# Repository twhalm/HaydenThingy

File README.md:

# Readme
- I am not a pro so I am sure things are a bit messy
- This uses KiCad 8.x
- The initial production and assembly quote was through JLCPCB
## Overview
If you want to get started and just view things in KiCad:
- Clone the repo
- Download KiCad
- Open the haydenThingy project

There will be a lot of stuff in the folder but there are really only two things to look at: the HaydenThingy schematic and pcb.  You can view those by opening the Schematic editor and the PCB editor.

## Initial version of the board
The first version of the board just combines the connections of the original three boards onto one PCB.  The ESP-32 and the LTE board attach via headers and the RS-485 breakout board was just incorporated into the PCB.

The larger board is a pretty simple board, all of the components are one once side, it is a large rectangle, and there are M3 holes for mounting on each corner.

## Next Steps
- Probably the first thing to do with this board is to order a low-volume run as a prototype to ensure everything fits/works as intended.

### Easy improvements to make
These are obvious and easy things that could be changed.
- The positioning of all of the components can be changed to make things slightly more compact or better
- You can make it more compact by mouting components on both sides (you can probably mount the LTE and ESP-32 boards on the front and back)
- Mounting holes can be changed and more can be added.

### Medium improvements to make?
- Put the battery connector on the PCB if it makes things easier
- Get rid of the screw terminal and put downstream components on the board directly (jst connectors for sensors, etc)

### Hard improvements
- Incorporate the ESP-32 and USB-C directly into the PCB
- Do the same for the LTE Board

## How do?
### Very brief KiCad workflow
1. Create a schematic. The Schematic has all of the components on a drawing and represents the various connections. To make a schematic you add **SYMBOLS**, which are essentially generic representations of various components. Once you have symbols you add connections between the various symbols.  You can draw wires on a schematic, but usually you use labels to keep things clean.
2. Associate your symbols with **FOOTPRINTS** a footprint is literally the physical footprint your component has on the PCB.  It is the size, pad, locations, etc.  For example you could have a generic symbol for a resistor in your schematic but you specify the physical shape of the resistor using a footprint.  For items like resistors there are a standard set of symbols and footprints that KiCad has in its builtin library.
3. Once you have a schematic and footprints you can create a PCB by laying out the footprints and drawing traces.

### Specifics to this board
- It is not normal for things to connect via headers since EEs know what they are doing.  The ESP-32 board had a footprint available from sparkfun since it fits one of their standard board layouts, but the LTE one did not and I had to make one.

- The

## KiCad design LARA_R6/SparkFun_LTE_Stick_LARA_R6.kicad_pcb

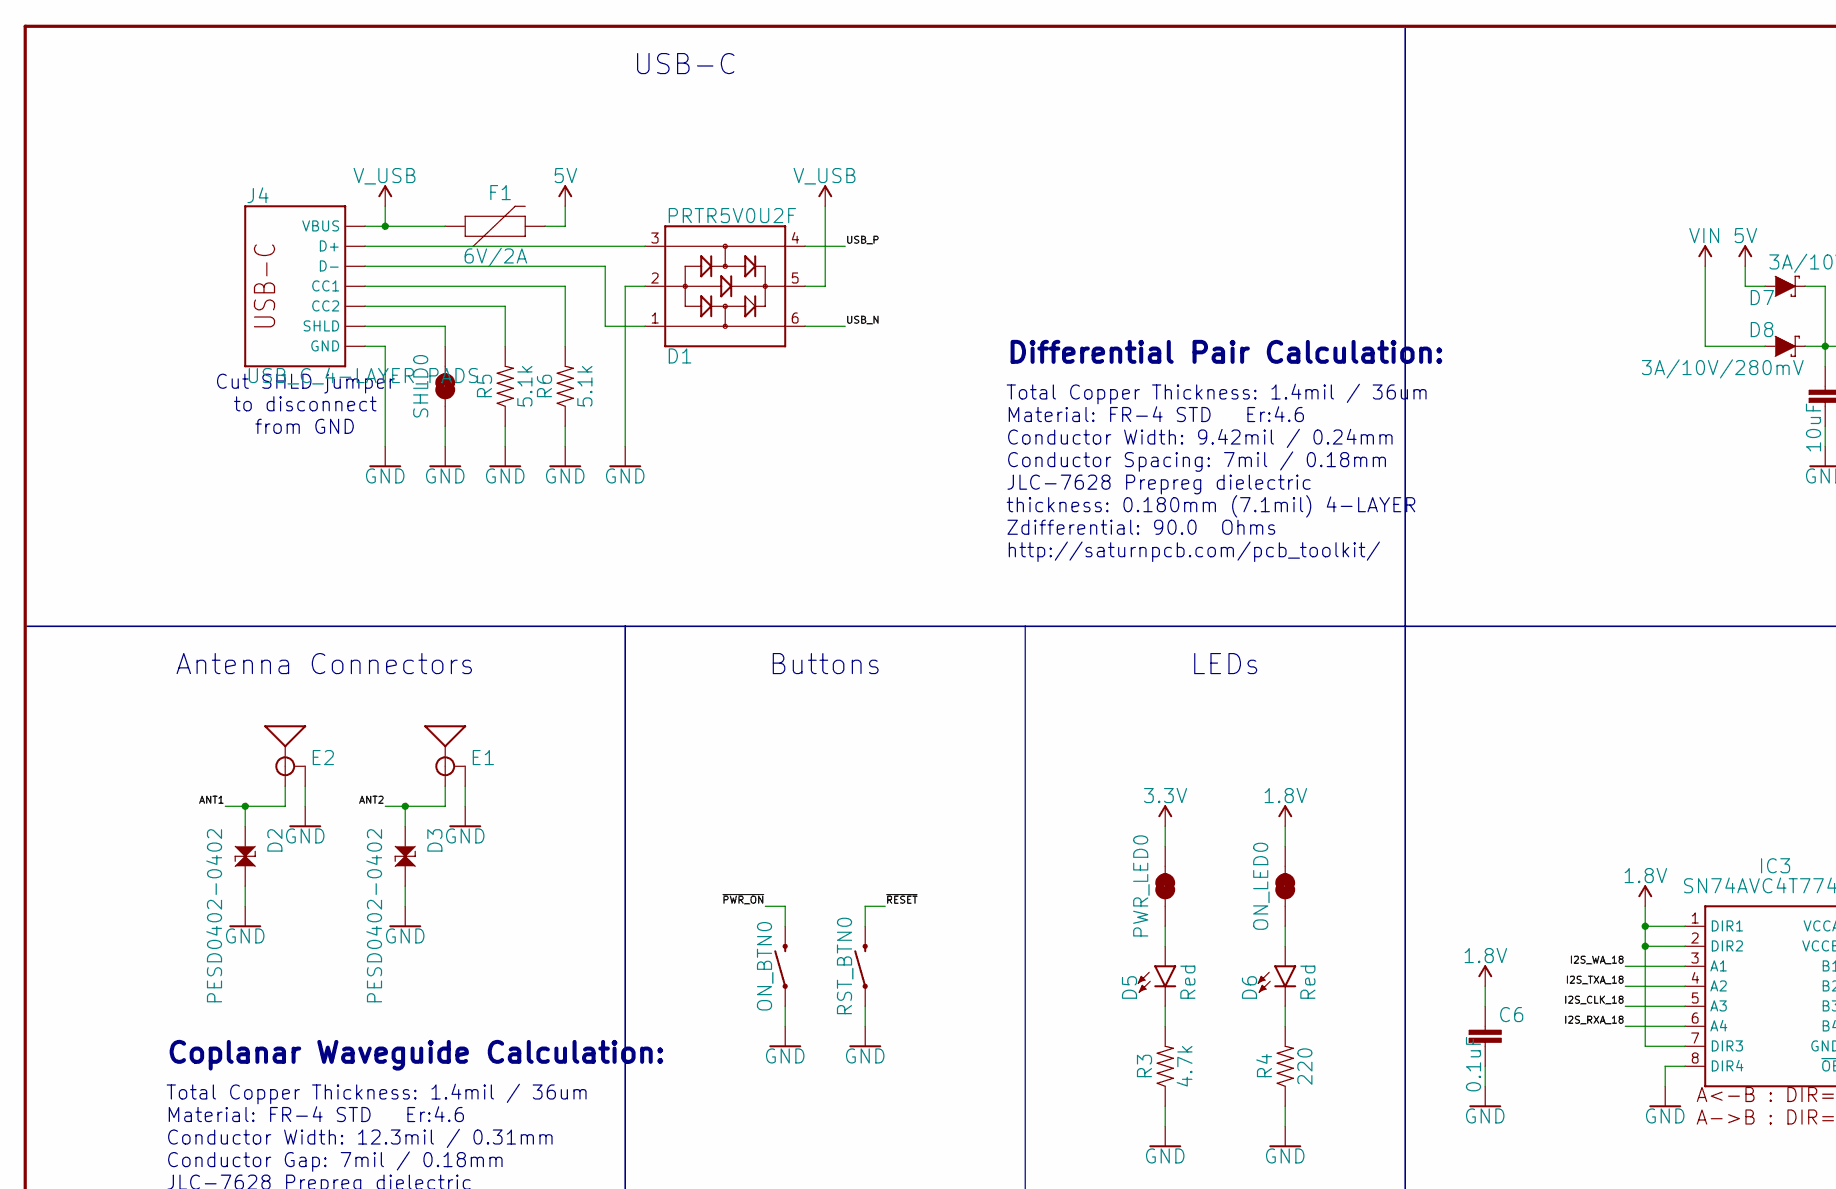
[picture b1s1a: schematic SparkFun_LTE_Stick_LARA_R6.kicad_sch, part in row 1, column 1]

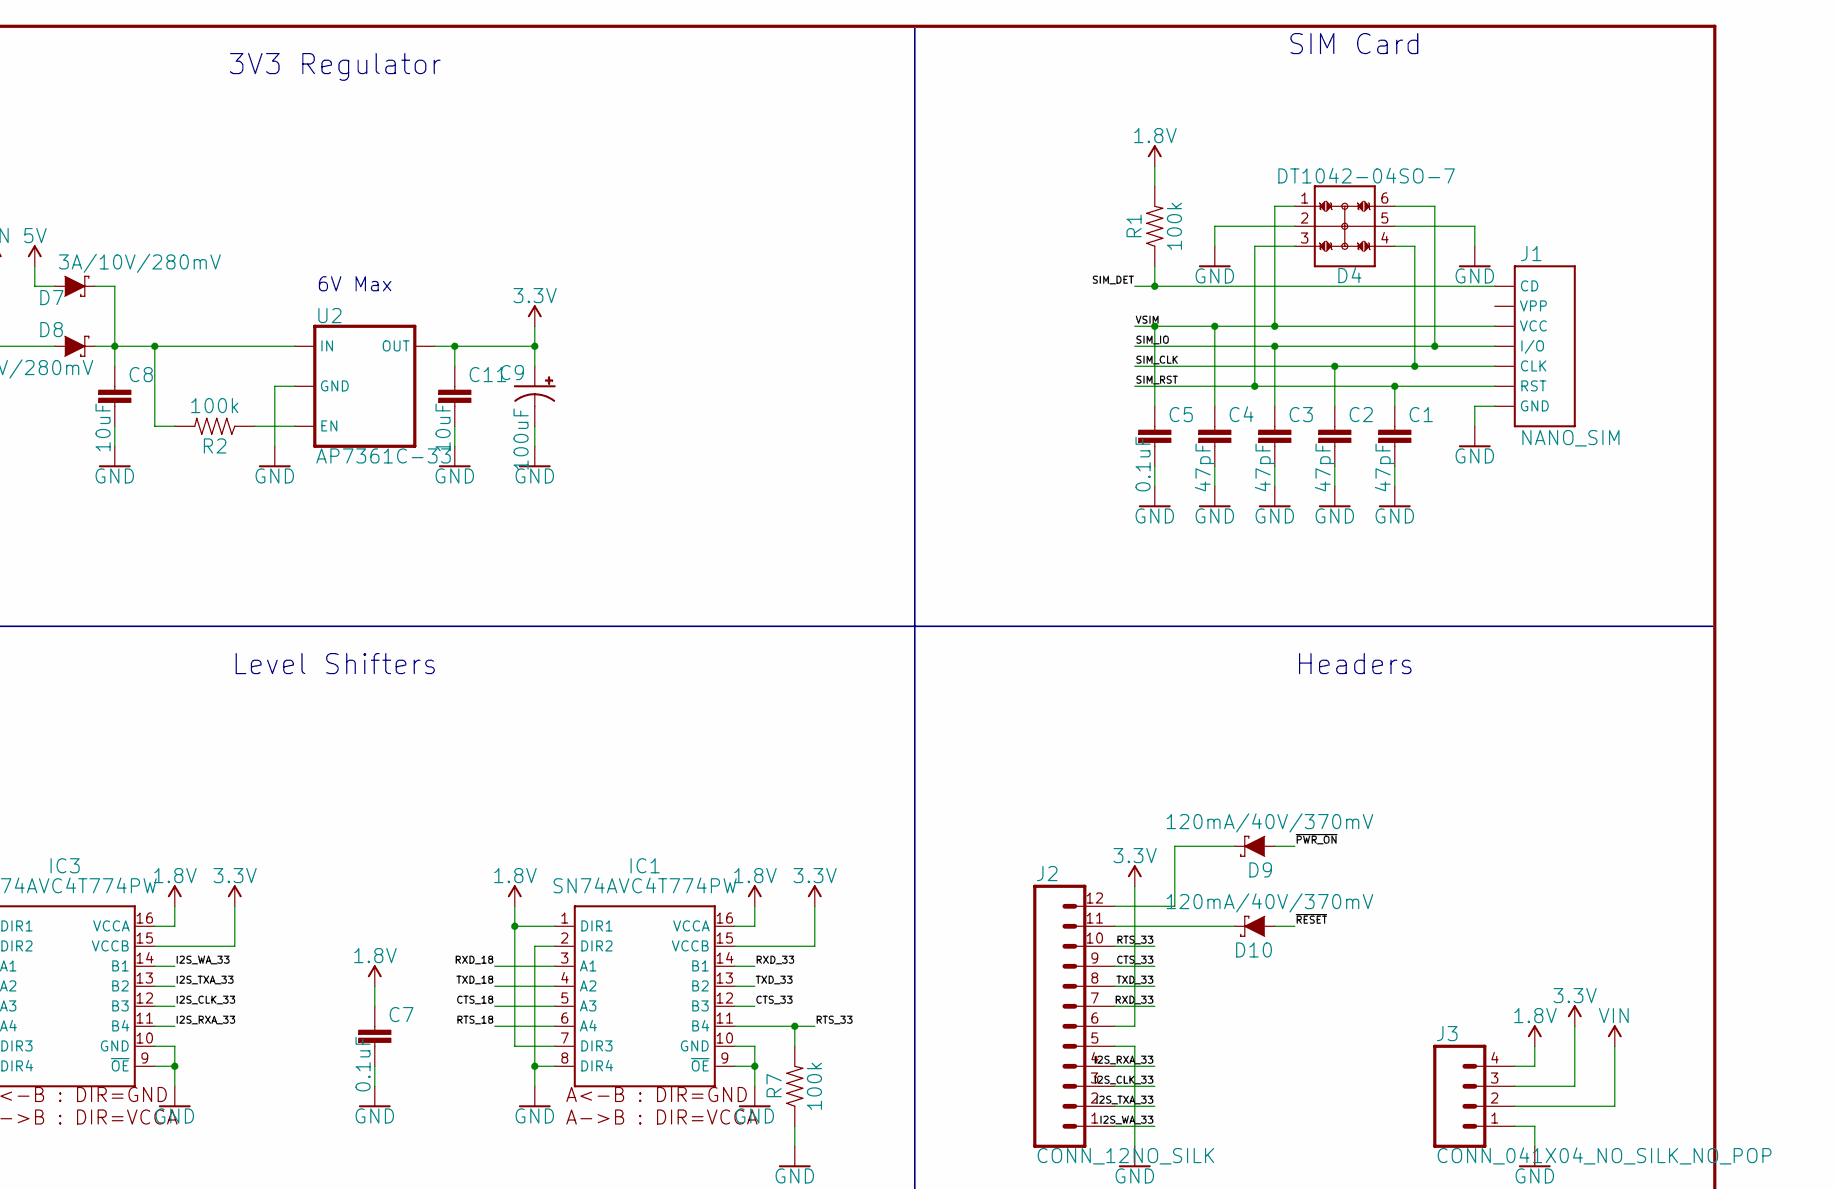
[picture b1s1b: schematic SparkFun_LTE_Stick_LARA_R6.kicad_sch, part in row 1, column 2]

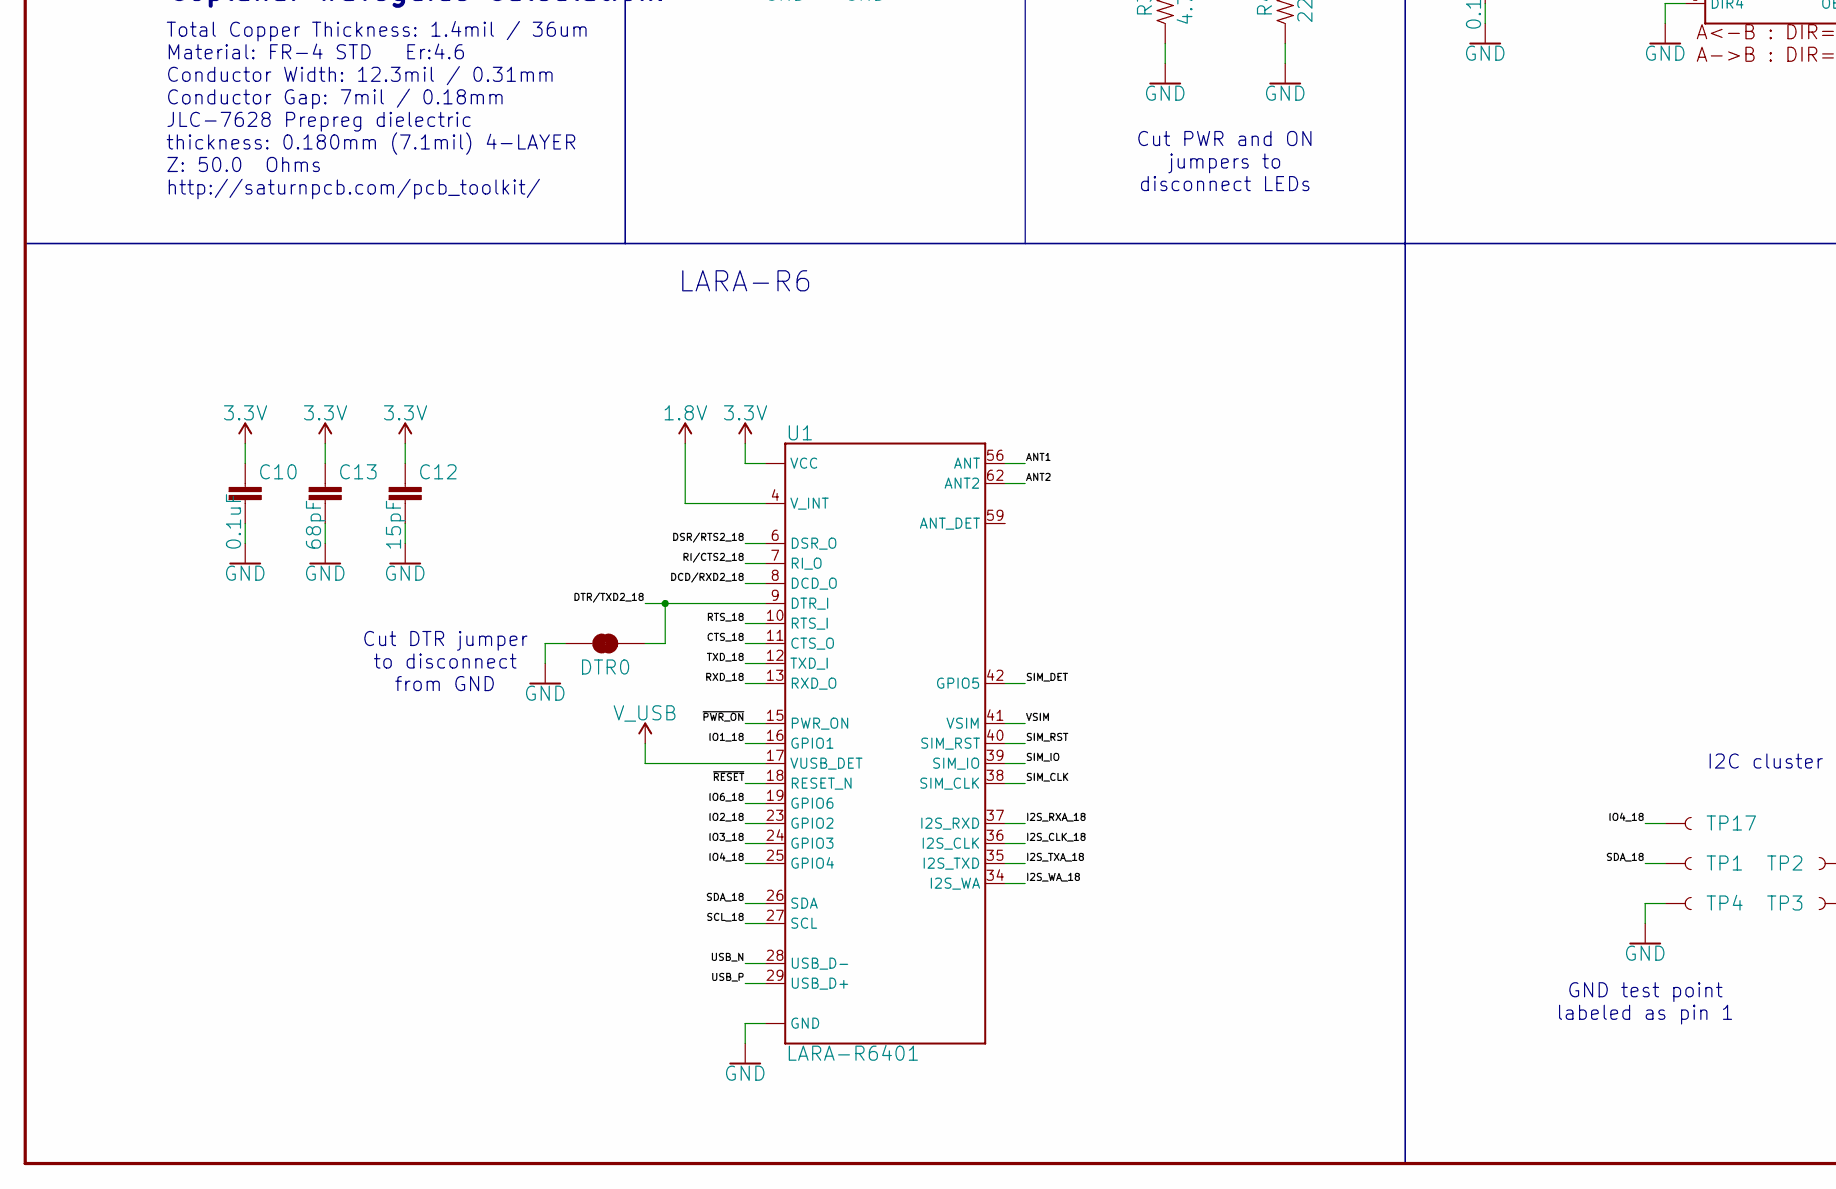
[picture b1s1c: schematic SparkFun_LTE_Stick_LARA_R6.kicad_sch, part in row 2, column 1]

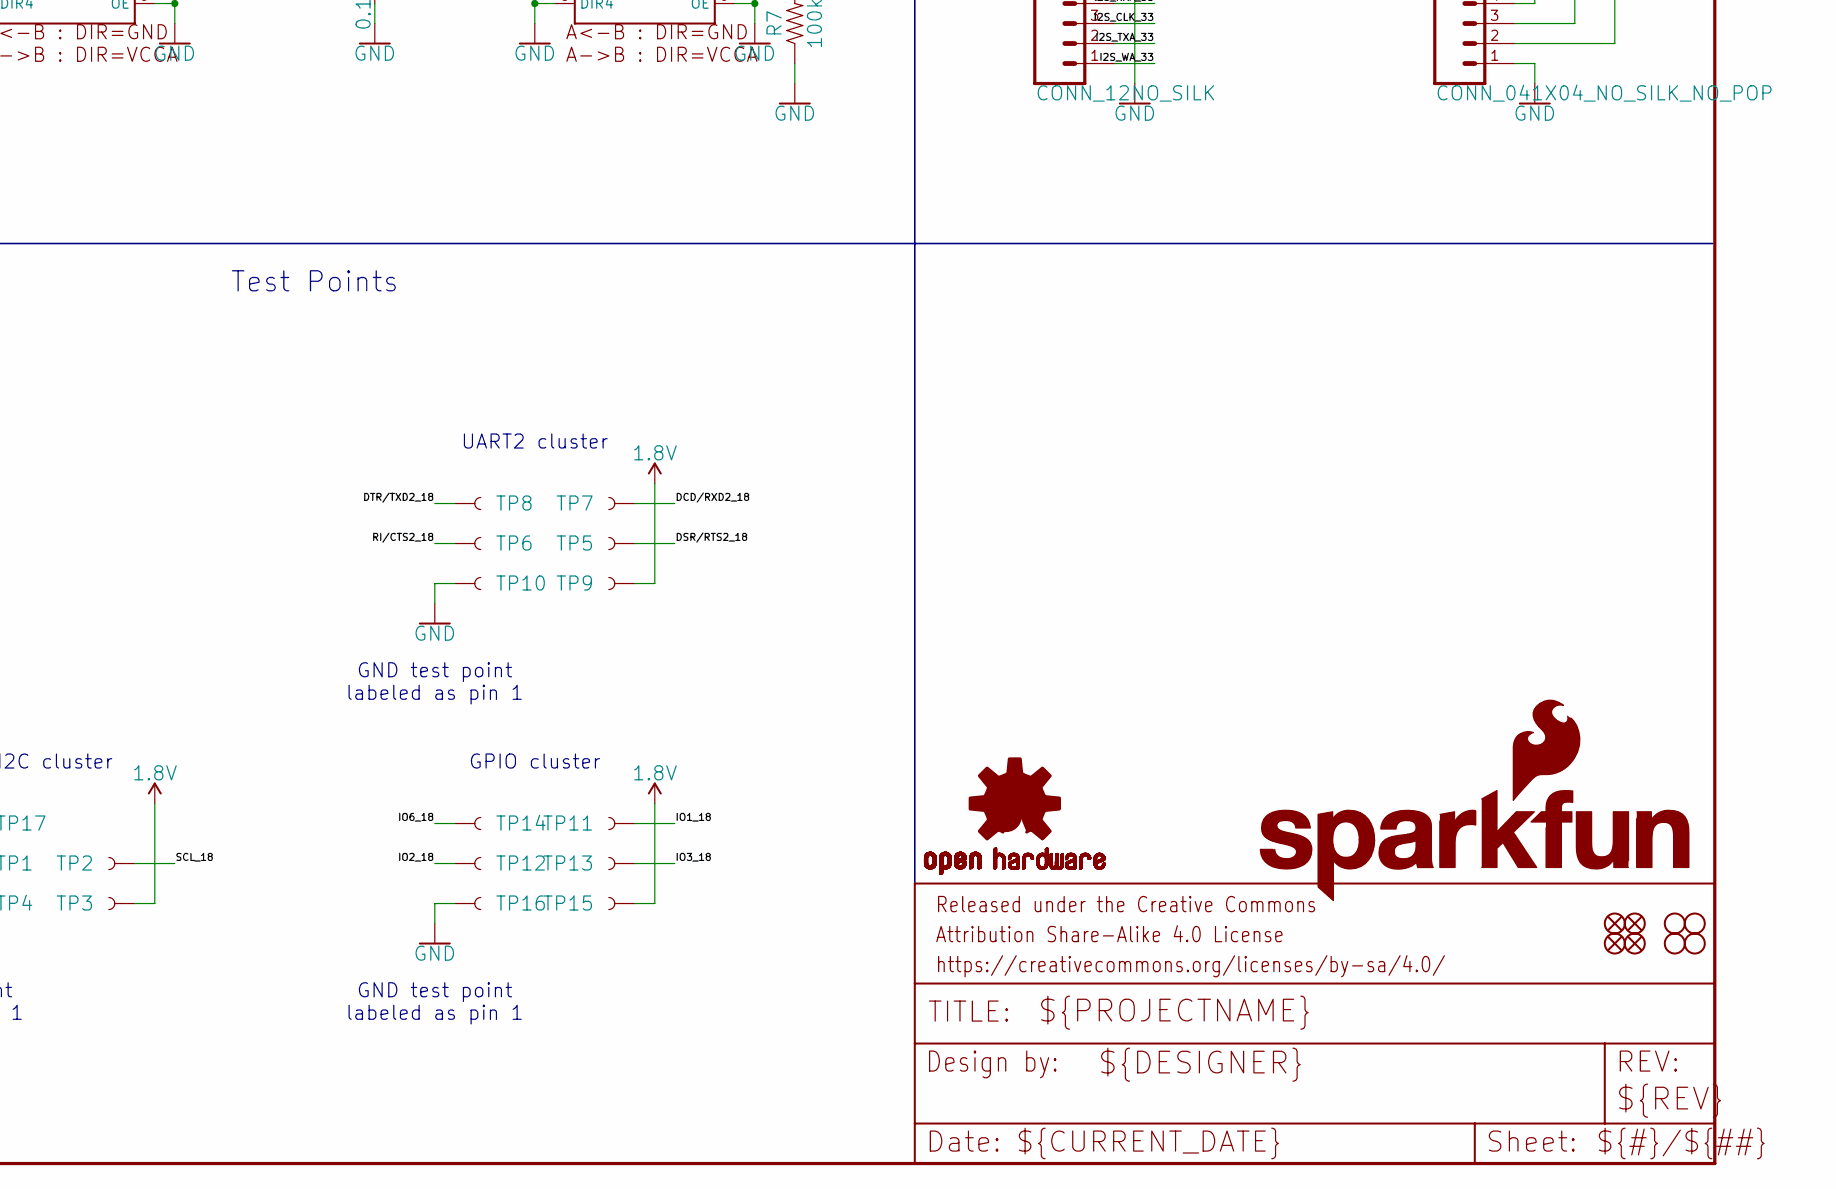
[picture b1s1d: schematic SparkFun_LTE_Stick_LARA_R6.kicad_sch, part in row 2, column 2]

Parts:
C1, C2, C3, C4: 47pF; 0603
C5, C6, C7, C10: 0.1uF; 0603
C8, C11: 10uF; 0805
C9: 100uF; PANASONIC_D
C12: 15pF; 0603
C13: 68pF; 0603
D1: PRTR5V0U2F; SOT886
D2, D3: PESD0402-0402; 0402
D4: DT1042-04SO-7; SOT23-6L
D5, D6: Red; LED-0603
D7, D8: 3A/10V/280mV; SOD-323
D9, D10: 120mA/40V/370mV; SOD-523
DTR0: JUMPER-SMT_2_NC_TRACE_SILK; SMT-JUMPER_2_NC_TRACE_SILK
E1, E2: ANTENNA-SMA-GROUNDEDEDGE_SMA; SMA-EDGE
F1: 6V/2A; 1210
FD1, FD2, FD3, FD4: FIDUCIAL1X2; FIDUCIAL-1X2
FRAME1: FRAME-LEDGER; CREATIVE_COMMONS
H1, H2, H3, H4: STAND-OFF
IC1, IC3: SN74AVC4T774PW; SOP65P640X120-16N
J1: NANO_SIM; NANO_SIM_PP
J2: CONN_12NO_SILK; 1X12_NO_SILK
J3: CONN_041X04_NO_SILK_NO_POP; 1X04_NO_SILK
J4: USB_C_4-LAYER_PADS; USB-C-16P_4LAYER-PADS
LOGO1: SFE_LOGO_NAME_FLAME.1_INCH; SFE_LOGO_NAME_FLAME_.1
LOGO2: OSHW-LOGOM; OSHW-LOGO-M
ON_BTN0: MOMENTARY-SWITCH-SPST-SMD-4.6X2.8MM; TACTILE_SWITCH_SMD_4.6X2.8MM
ON_LED0: JUMPER-SMT_2_NC_TRACE_SILK; SMT-JUMPER_2_NC_TRACE_SILK
PWR_LED0: JUMPER-SMT_2_NC_TRACE_SILK; SMT-JUMPER_2_NC_TRACE_SILK
R1, R2, R7: 100k; 0603
R3: 4.7k; 0603
R4: 220; 0603
R5, R6: 5.1k; 0603
RST_BTN0: MOMENTARY-SWITCH-SPST-SMD-4.6X2.8MM; TACTILE_SWITCH_SMD_4.6X2.8MM
SHLD0: JUMPER-SMT_2_NC_TRACE_SILK; SMT-JUMPER_2_NC_TRACE_SILK
TP1, TP2, TP3, TP4, TP5, TP6, TP7, TP8, TP9, TP10, TP11, TP12, TP13, TP14, TP15, TP16, TP17: TEST-POINT3X5; PAD.03X.05
U1: LARA-R6401; LARA-LGA
U2: AP7361C-33; UDFN-8

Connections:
1.8V: C6.1, C7.1, IC1.1 (DIR1), IC1.7 (DIR3), IC1.16 (VCCA), IC3.1 (DIR1), IC3.2 (DIR2), IC3.7 (DIR3), IC3.16 (VCCA), J3.4, ON_LED0.2, R1.2, TP3.1, TP9.1, TP15.1, U1.4 (V_INT)
3.3V: C9.+, C10.1, C11.1, C12.1, C13.1, IC1.15 (VCCB), IC3.15 (VCCB), J2.6, J3.3, PWR_LED0.2, U1.51 (VCC), U1.52 (VCC), U1.53 (VCC), U2.1 (OUT)
5V: D7.A, F1.2
ANT1: D2.1, E2.SIG (SIGNAL), U1.56 (ANT)
ANT2: D3.1, E1.SIG (SIGNAL), U1.62 (ANT2)
CTS_18: IC1.5 (A3), U1.11 (CTS_O)
CTS_33: IC1.12 (B3), J2.9
DCD/RXD2_18: TP7.1, U1.8 (DCD_O)
DSR/RTS2_18: TP5.1, U1.6 (DSR_O)
DTR/TXD2_18: DTR0.2, TP8.1, U1.9 (DTR_I)
EN: R2.1, U2.5 (EN)
GND: C1.2, C2.2, C3.2, C4.2, C5.2, C6.2, C7.2, C8.2, C9.-, C10.2, C11.2, C12.2, C13.2, D1.2, D2.2, D3.2, D4.2, D4.5, DTR0.1, E1.GND@0 (GND), E1.GND@1 (GND), E1.GND@2 (GND), E1.GND@3 (GND), E2.GND@0 (GND), E2.GND@1 (GND), E2.GND@2 (GND), E2.GND@3 (GND), IC1.2 (DIR2), IC1.8 (DIR4), IC1.9 (~OE), IC1.10 (GND), IC3.8 (DIR4), IC3.9 (~OE), IC3.10 (GND), J1.A1 (GND), J1.A2 (GND), J1.A3 (GND), J1.A4 (GND), J1.C5 (GND), J2.5, J3.1, J4.GND, J4.GND2 (GND), ON_BTN0.1, ON_BTN0.2 (1), R3.1, R4.1, R5.1, R6.1, R7.1, RST_BTN0.1, RST_BTN0.2 (1), SHLD0.1, TP4.1, TP10.1, TP16.1, U1.1 (GND), U1.3 (GND), U1.5 (GND), U1.14 (GND), U1.20 (GND), U1.21 (GND), U1.22 (GND), U1.30 (GND), U1.32 (GND), U1.43 (GND), U1.50 (GND), U1.54 (GND), U1.55 (GND), U1.57 (GND), U1.58 (GND), U1.60 (GND), U1.61 (GND), U1.63 (GND), U1.64 (GND), U1.65 (GND), U1.66 (GND), U1.67 (GND), U1.68 (GND), U1.69 (GND), U1.70 (GND), U1.71 (GND), U1.72 (GND), U1.73 (GND), U1.74 (GND), U1.75 (GND), U1.76 (GND), U1.77 (GND), U1.78 (GND), U1.79 (GND), U1.80 (GND), U1.81 (GND), U1.82 (GND), U1.83 (GND), U1.84 (GND), U1.85 (GND), U1.86 (GND), U1.87 (GND), U1.88 (GND), U1.89 (GND), U1.90 (GND), U1.91 (GND), U1.92 (GND), U1.93 (GND), U1.94 (GND), U1.95 (GND), U1.96 (GND), U2.4 (GND), U2.EP (GND)
I2S_CLK_18: IC3.5 (A3), U1.36 (I2S_CLK)
I2S_CLK_33: IC3.12 (B3), J2.3
I2S_RXA_18: IC3.6 (A4), U1.37 (I2S_RXD)
I2S_RXA_33: IC3.11 (B4), J2.4
I2S_TXA_18: IC3.4 (A2), U1.35 (I2S_TXD)
I2S_TXA_33: IC3.13 (B2), J2.2
I2S_WA_18: IC3.3 (A1), U1.34 (I2S_WA)
I2S_WA_33: IC3.14 (B1), J2.1
IO1_18: TP11.1, U1.16 (GPIO1)
IO2_18: TP12.1, U1.23 (GPIO2)
IO3_18: TP13.1, U1.24 (GPIO3)
IO4_18: TP17.1, U1.25 (GPIO4)
IO6_18: TP14.1, U1.19 (GPIO6)
unnamed: D5.C, R3.2
unnamed: D5.A, PWR_LED0.1
unnamed: D6.A, ON_LED0.1
unnamed: D6.C, R4.2
unnamed: D10.C, J2.11
unnamed: D9.C, J2.12
unnamed: C8.1, D7.C, D8.C, R2.2, U2.8 (IN)
unnamed: J4.B5 (CC2), R5.2
unnamed: J4.A5 (CC1), R6.2
unnamed: D1.3, J4.A6 (D+), J4.B6 (D+)
unnamed: D1.1, J4.A7 (D-), J4.B7 (D-)
RI/CTS2_18: TP6.1, U1.7 (RI_O)
RTS_18: IC1.6 (A4), U1.10 (RTS_I)
RTS_33: IC1.11 (B4), J2.10, R7.2
RXD_18: IC1.3 (A1), U1.13 (RXD_O)
RXD_33: IC1.14 (B1), J2.7
SCL_18: TP2.1, U1.27 (SCL)
SDA_18: TP1.1, U1.26 (SDA)
SHLD: J4.SHLD1 (SHLD), J4.SHLD2 (SHLD), J4.SHLD3 (SHLD), J4.SHLD4 (SHLD), SHLD0.2
SIM_CLK: C2.1, D4.4, J1.C3 (CLK), U1.38 (SIM_CLK)
SIM_DET: J1.CD, R1.1, U1.42 (GPIO5)
SIM_IO: C3.1, D4.6, J1.C7 (I/O), U1.39 (SIM_IO)
SIM_RST: C1.1, D4.3, J1.C2 (RST), U1.40 (SIM_RST)
TXD_18: IC1.4 (A2), U1.12 (TXD_I)
TXD_33: IC1.13 (B2), J2.8
USB_N: D1.6, U1.28 (USB_D-)
USB_P: D1.4, U1.29 (USB_D+)
VIN: D8.A, J3.2
VSIM: C4.1, C5.1, D4.1, J1.C1 (VCC), U1.41 (VSIM)
V_USB: D1.5, F1.1, J4.VBUS1 (VBUS), J4.VBUS2 (VBUS), U1.17 (VUSB_DET)
~PWR_ON: D9.A, ON_BTN0.3 (2), ON_BTN0.4 (2), U1.15 (PWR_ON)
~RESET: D10.A, RST_BTN0.3 (2), RST_BTN0.4 (2), U1.18 (RESET_N)

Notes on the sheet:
LARA-R6
I2C cluster
GPIO cluster
Headers
Total Copper Thickness: 1.4mil / 36um Material: FR-4 STD Er:4.6 Conductor Width: 9.42mil / 0.24mm Conductor Spacing: 7mil / 0.18mm JLC-7628 Prepreg dielectric thickness: 0.180mm (7.1mil) 4-LAYER Zdifferential: 90.0 Ohms http://saturnpcb.com/pcb_toolkit/
LEDs
Buttons
SIM Card
GND test point labeled as pin 1
Level Shifters
UART2 cluster
3V3 Regulator
Test Points
USB-C
Coplanar Waveguide Calculation:
Differential Pair Calculation:
Total Copper Thickness: 1.4mil / 36um Material: FR-4 STD Er:4.6 Conductor Width: 12.3mil / 0.31mm Conductor Gap: 7mil / 0.18mm JLC-7628 Prepreg dielectric thickness: 0.180mm (7.1mil) 4-LAYER Z: 50.0 Ohms http://saturnpcb.com/pcb_toolkit/
6V Max~{}
Antenna Connectors
Cut PWR and ON jumpers to disconnect LEDs
Cut SHLD jumper to disconnect from GND
Cut DTR jumper to disconnect from GND

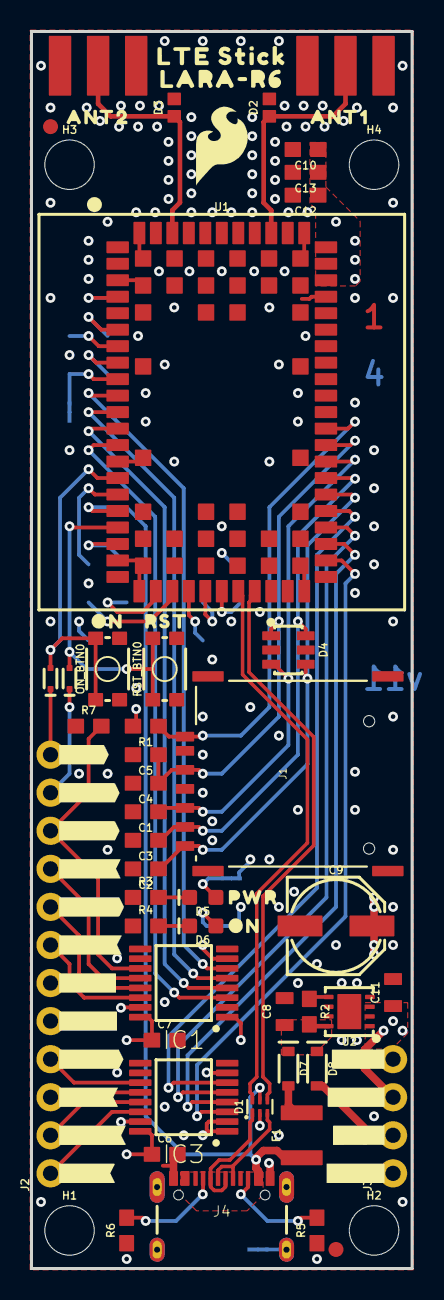
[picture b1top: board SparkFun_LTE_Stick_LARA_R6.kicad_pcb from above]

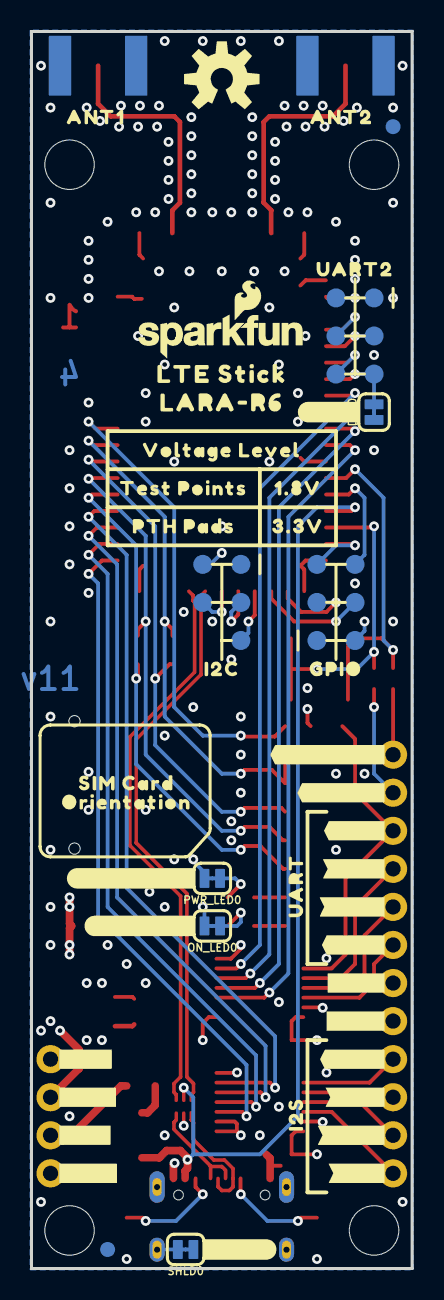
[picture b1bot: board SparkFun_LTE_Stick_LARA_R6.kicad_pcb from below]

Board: 4 copper layers, 25.4 x 82.6 mm, 137 parts (61 on the bottom side), 57 nets.

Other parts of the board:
U$1, U$25: LTE_STICK0
U$2: SFE_LOGO_FLAME_.2
U$3, U$15: #_3V3#0
U$4, U$5: #_GND#0
U$6: #SHLD#0
U$7, U$8: #GND_#0
U$9, U$12: #3V3_#0
U$10: #DTR#0
U$11: #VIN_#0
U$13: #1V8_#0
U$14: #_1V8#0
U$16: #_VIN#0
U$17: #_CTS#0
U$18: #_RTS#0
U$19: #RXD_#0
U$20: #TXD_#0
U$21: #_CLK#0
U$22: #_WA#0
U$23: #RXA_#0
U$24: #TXA_#0
U$26: SIM_CARD0
U$27: VOLTAGE_LEVEL0
U$28: PWR0
U$29, U$36: ANT10
U$30: TEST_POINTS0
U$31, U$35: LARA#R60
U$32: #_RXA#0
U$33: #_#RST##0
U$34: PTH_PADS0
U$37, U$39: ON0
U$38: ##PWR_ON#_#0
U$40: #_TXA#0
U$41: #_TXD#0
U$42: #_RXD#0
U$43: #CLK_#0
U$44: #WA_#0
U$45: #RTS_#0
U$46: #CTS_#0
U$47: ##RESET#_#0
U$48: UART0
U$49: I2S0
U$50: 1#8V0
U$51: ORIENTATION0
U$52: RST0
U$53: #ON_LED#0
U$54: 3#3V0
U$55: ORDERING_INSTRUCTIONS
U$56: UART20
U$57: GPIO0
U$58: I2C0
U$59: #_#ON##0
U$60: #PWR_LED#0
U$61, U$62: ANT20

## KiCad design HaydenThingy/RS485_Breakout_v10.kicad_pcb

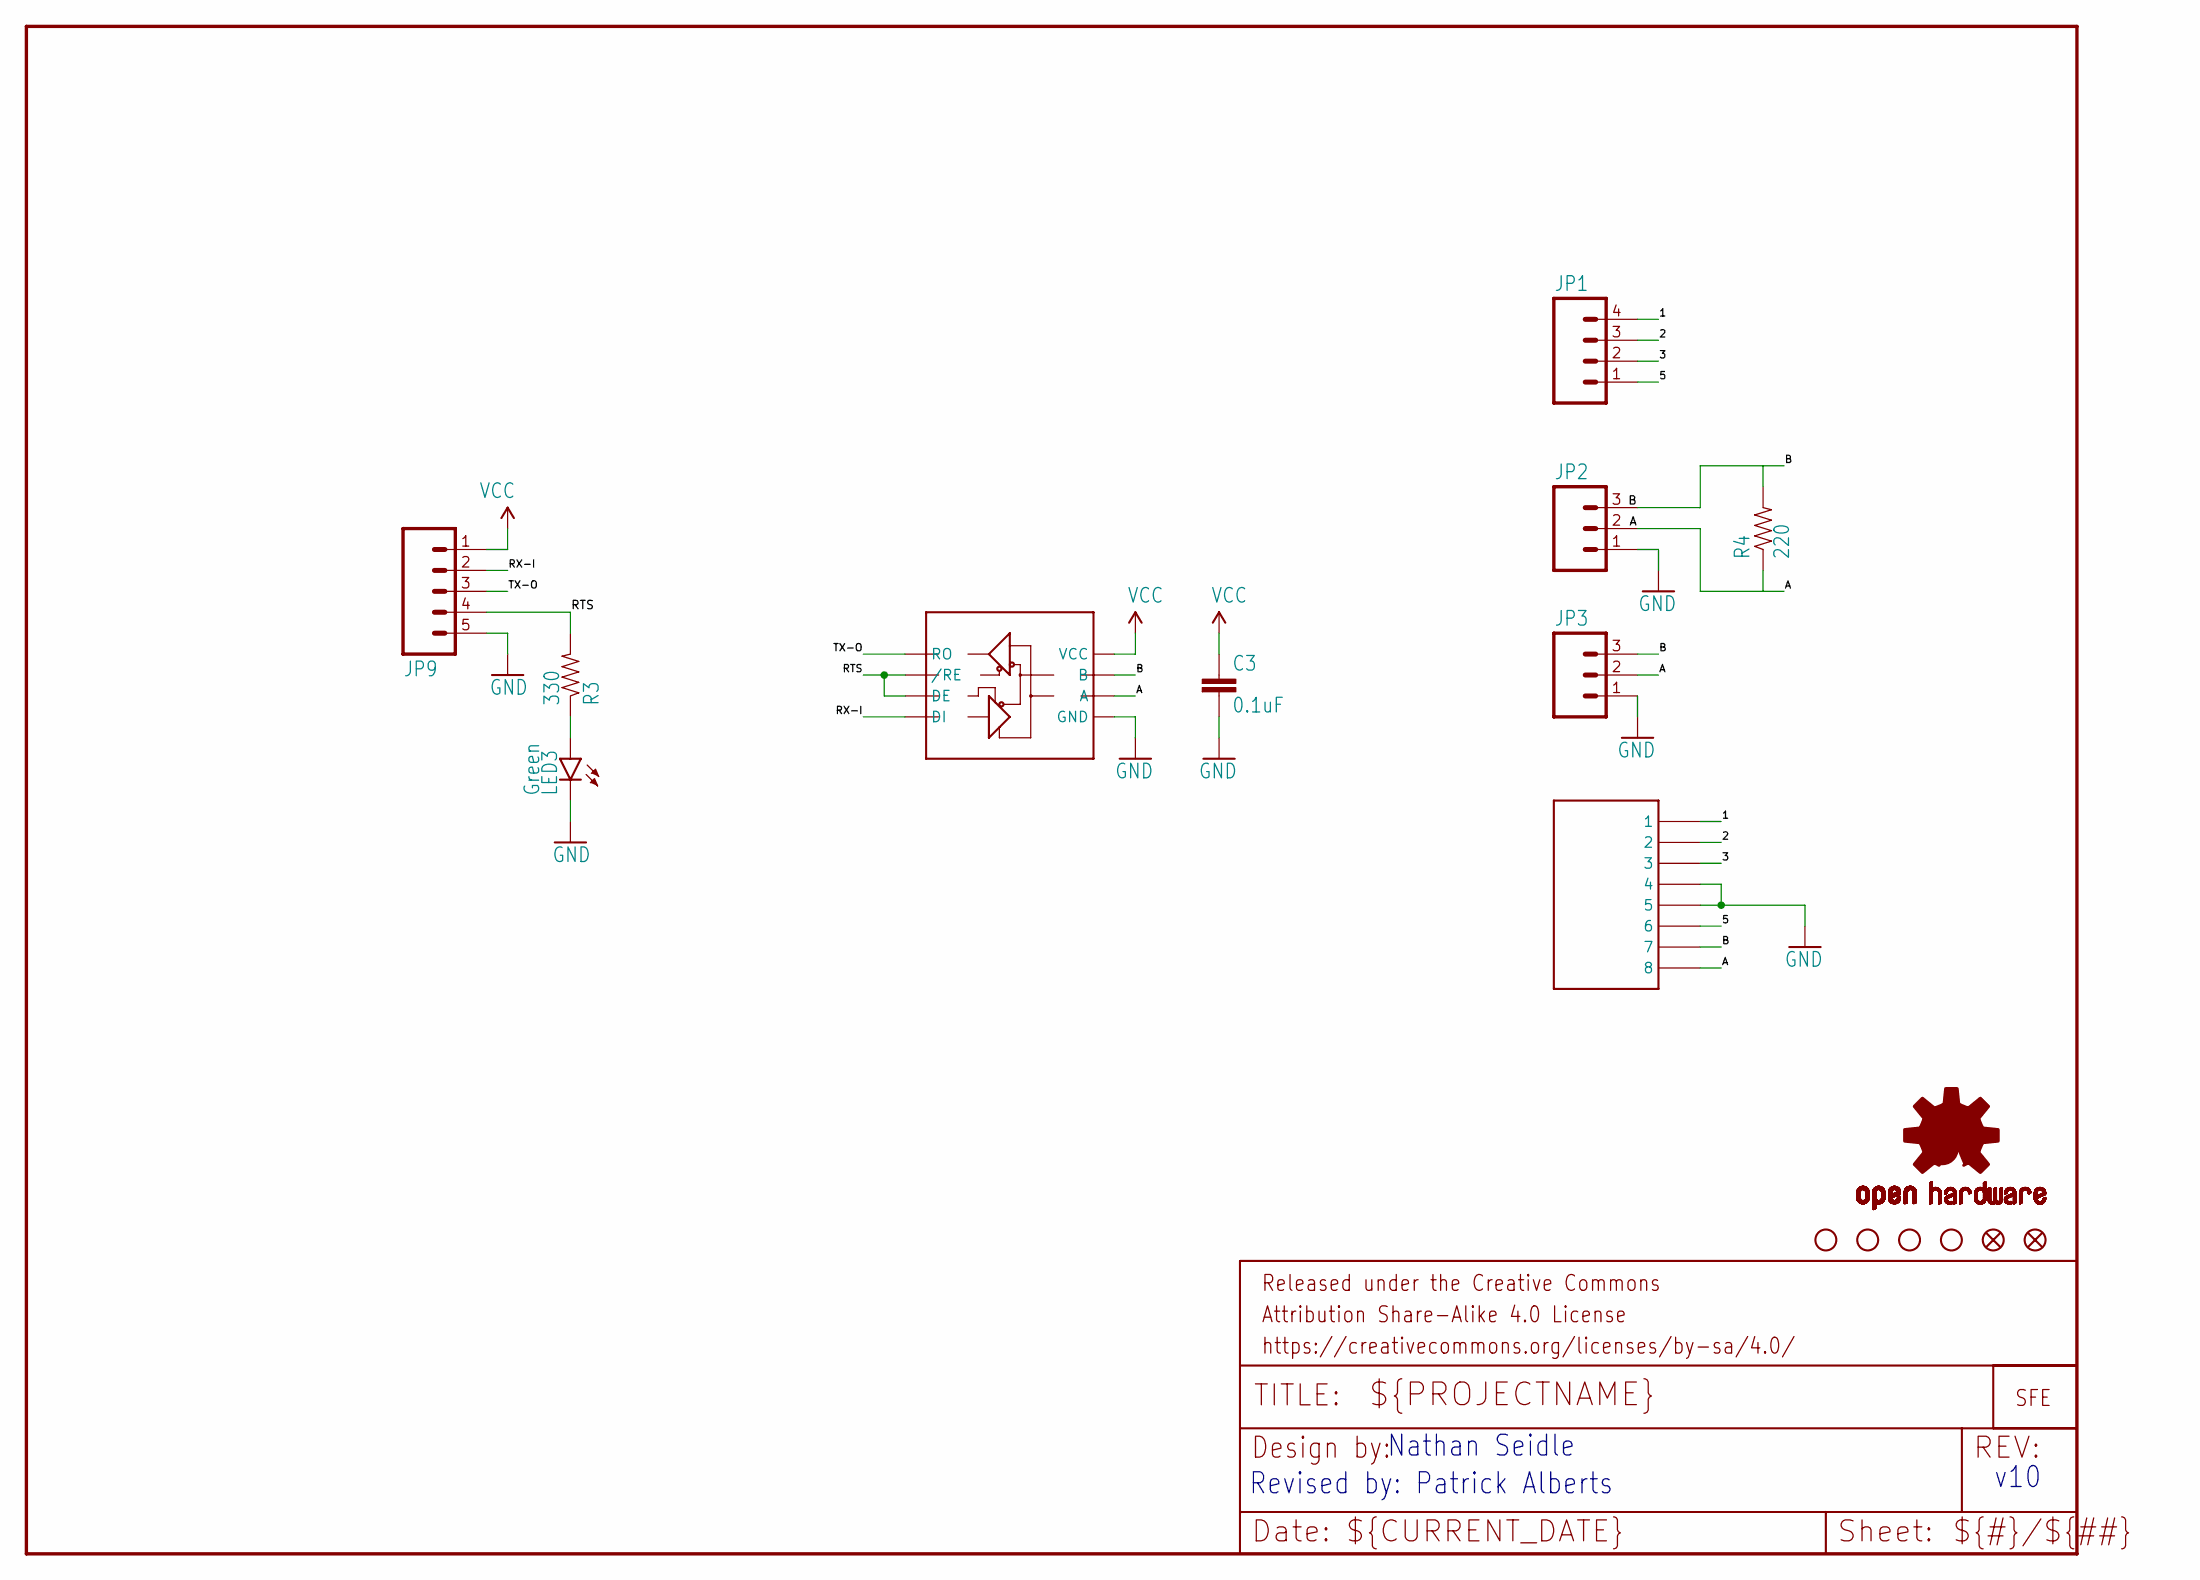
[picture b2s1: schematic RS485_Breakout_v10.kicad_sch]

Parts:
C3: 0.1uF; 0603-CAP
FRAME1: FRAME-LETTER; CREATIVE_COMMONS
JP1: M04PTH; 1X04
JP2: M03SCREW; SCREWTERMINAL-3.5MM-3
JP3: M03PTH; 1X03
JP4: RJ45-8PTH; RJ45-8
JP5, JP10: FIDUCIAL1X2; FIDUCIAL-1X2
JP6, JP7, JP8, JP15: STAND-OFF
JP9: M05PTH; 1X05
LED3: Green; LED-0603
LOGO1: OSHW-LOGOS; OSHW-LOGO-S
R3: 330; 0603-RES
R4: 220; 0603-RES
U2: RS485SOIC; SO08
U$2: LOGO-SFESK; SFE-LOGO-FLAME

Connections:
1: JP1.4, JP4.1
2: JP1.3, JP4.2
3: JP1.2, JP4.3
5: JP1.1, JP4.6
A: JP2.2, JP3.2, JP4.8, R4.1, U2.6 (A)
B: JP2.3, JP3.3, JP4.7, R4.2, U2.7 (B)
GND: C3.2, JP2.1, JP3.1, JP4.4, JP4.5, JP9.5, LED3.C, U2.5 (GND)
unnamed: LED3.A, R3.1
RTS: JP9.4, R3.2, U2.2 (/RE), U2.3 (DE)
RX-I: JP9.2, U2.4 (DI)
TX-O: JP9.3, U2.1 (RO)
VCC: C3.1, JP9.1, U2.8 (VCC)

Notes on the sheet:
v10
Nathan Seidle
Revised by: Patrick Alberts

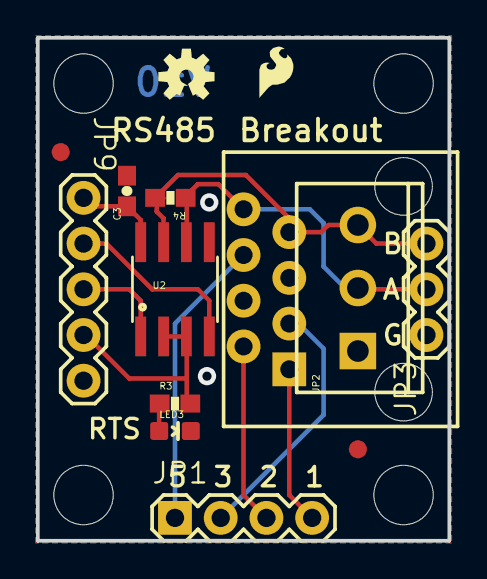
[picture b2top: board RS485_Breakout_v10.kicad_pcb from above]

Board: 2 copper layers, 22.9 x 27.9 mm, 19 parts (0 on the bottom side), 12 nets.

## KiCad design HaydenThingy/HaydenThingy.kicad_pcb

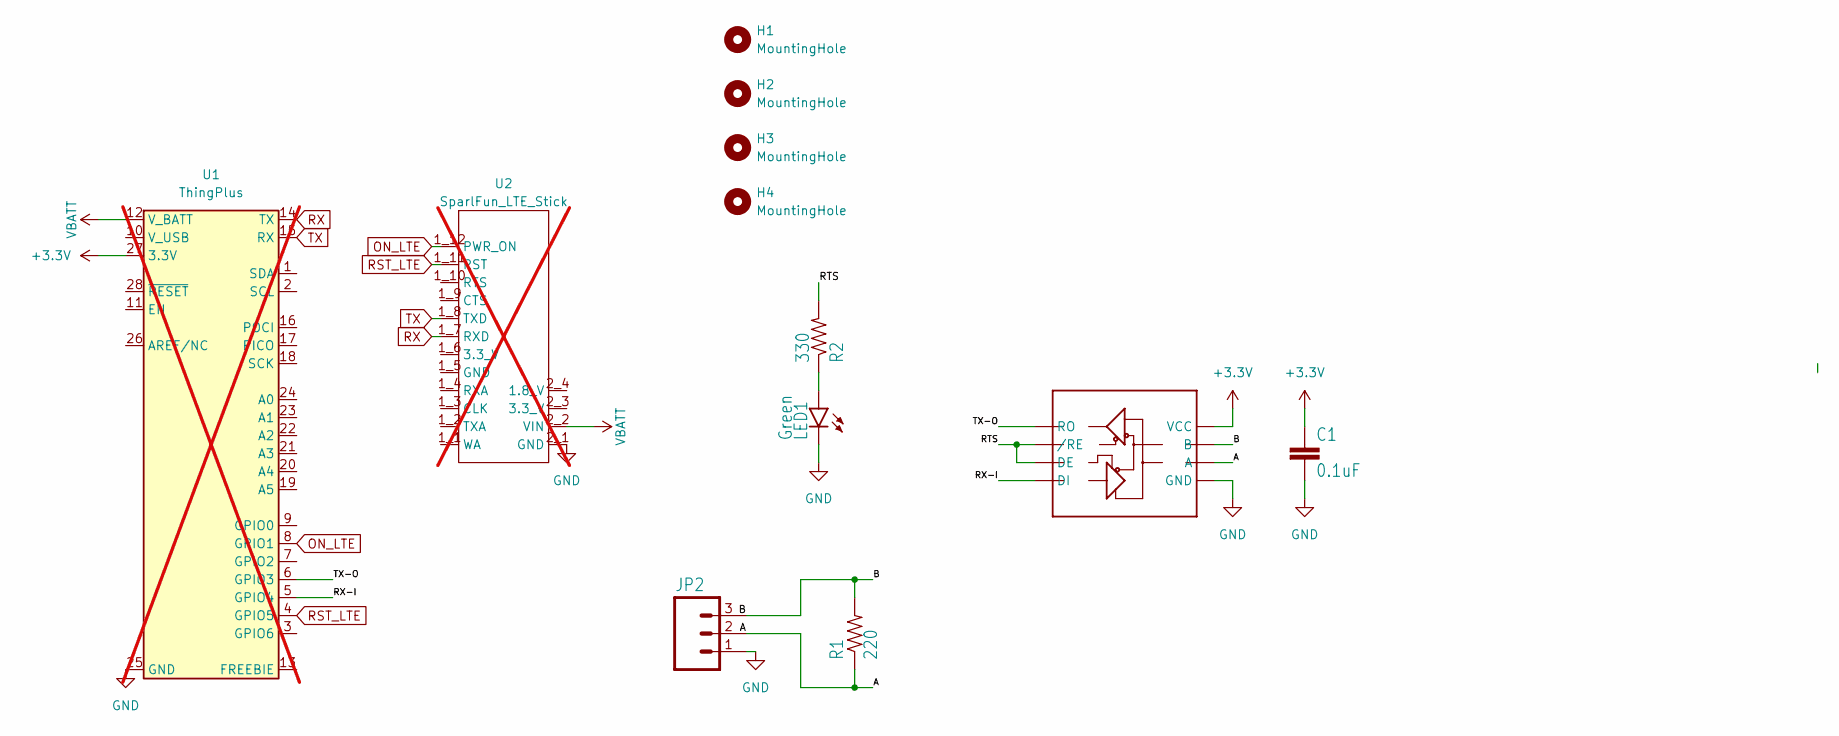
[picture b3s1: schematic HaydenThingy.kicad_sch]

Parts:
C1: 0.1uF; 0603-CAP
H1, H2, H3, H4: MountingHole; Standoff
JP2: M03SCREW; SCREWTERMINAL-3.5MM-3
LED1: Green; LED-0603
R1: 220; 0603-RES
R2: 330; 0603-RES
U1: ThingPlus; ThingPlus_With_Connectors; not fitted
U2: SparlFun_LTE_Stick; SparkFun_LTE_Stick; not fitted
U3: RS485SOIC; SO08

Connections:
+3.3V: C1.1, U1.27 (3.3V), U3.8 (VCC)
/A: JP2.2, R1.1, U3.6 (A)
/B: JP2.3, R1.2, U3.7 (B)
/RTS: R2.2, U3.2 (/RE), U3.3 (DE)
/RX-I: U1.5 (GPIO4), U3.4 (DI)
/TX-O: U1.6 (GPIO3), U3.1 (RO)
GND: C1.2, JP2.1, LED1.C, U1.25 (GND), U2.2_1 (GND), U3.5 (GND)
unnamed: LED1.A, R2.1
ON_LTE: U1.8 (GPIO1), U2.1_12 (PWR_ON)
RST_LTE: U1.4 (GPIO5), U2.1_11 (RST)
RX: U1.14 (TX), U2.1_7 (RXD)
TX: U1.15 (RX), U2.1_8 (TXD)
VBATT: U1.12 (V_BATT), U2.2_2 (VIN)

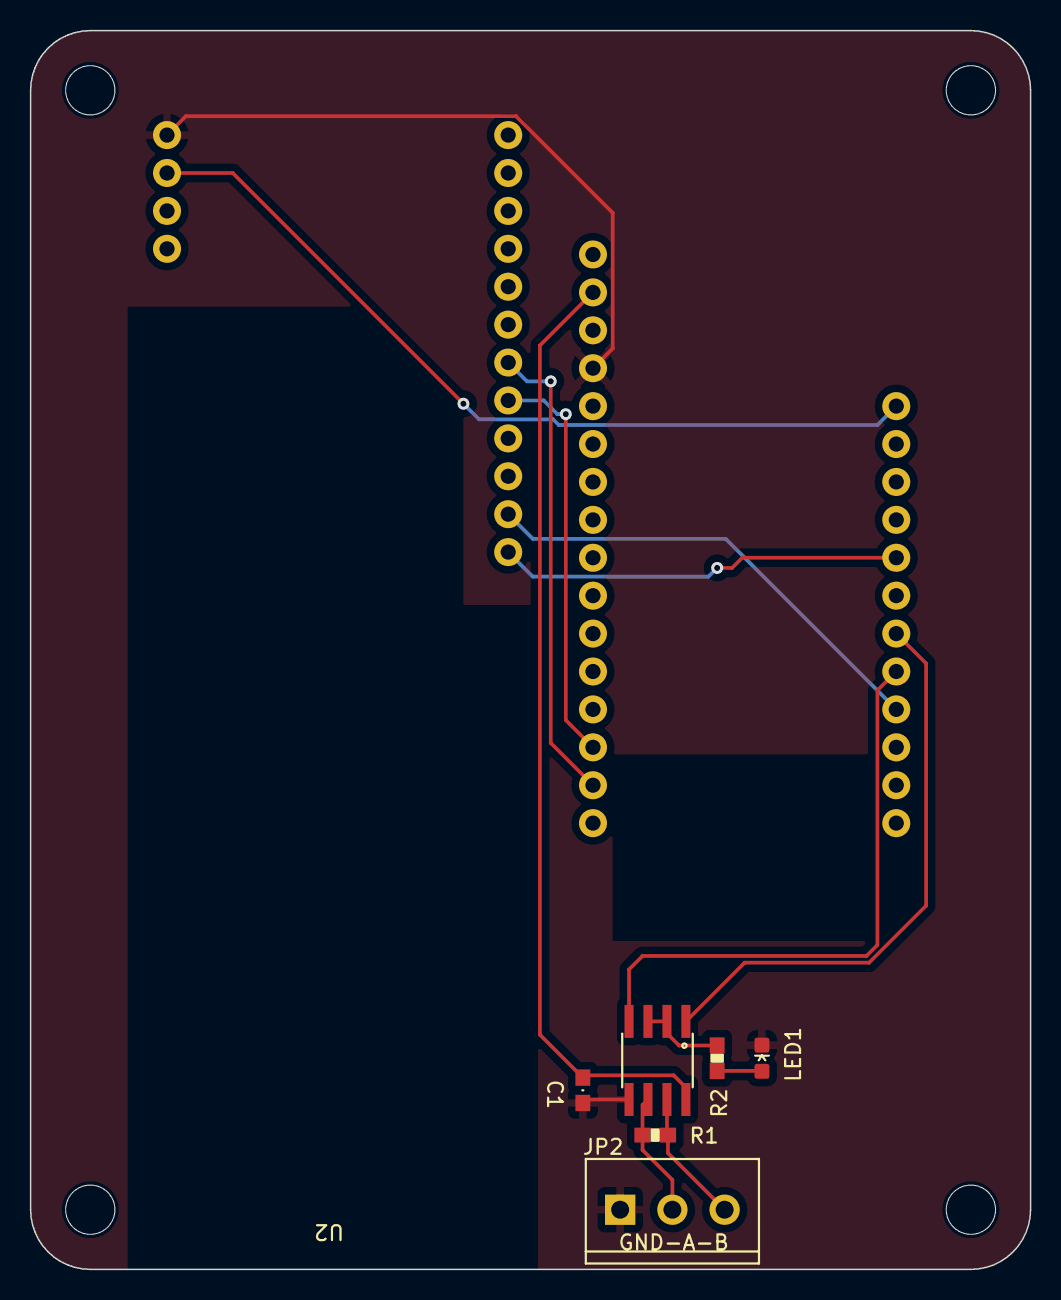
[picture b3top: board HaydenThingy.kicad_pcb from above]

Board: 2 copper layers, 67.0 x 83.0 mm, 12 parts (0 on the bottom side), 13 nets.

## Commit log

2024-07-28 initial?
2024-07-28 cleaning things up

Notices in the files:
HaydenThingy/RS485_Breakout_v10.kicad_sch:
https://creativecommons.org/licenses/by-sa/4.0
Released under the Creative Commons
parts and their libraries:
Released under the Creative Commons Attribution Share-Alike 4.0 License
